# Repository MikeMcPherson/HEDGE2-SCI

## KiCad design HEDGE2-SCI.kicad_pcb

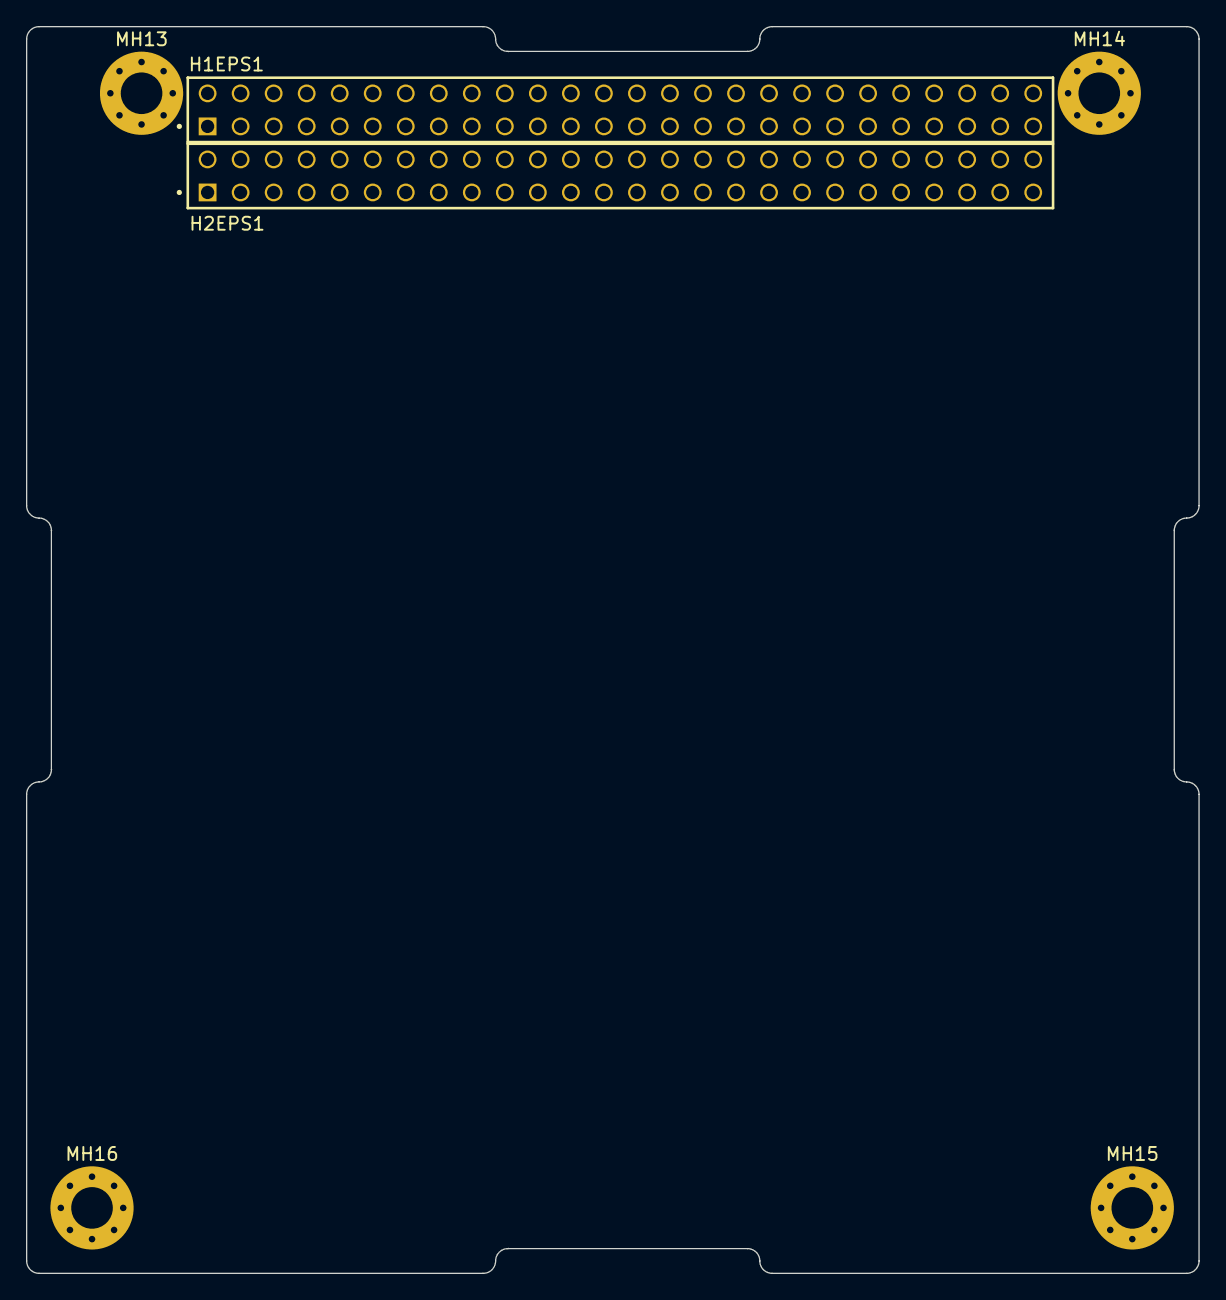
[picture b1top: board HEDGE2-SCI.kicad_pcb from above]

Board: 4 copper layers, 90.2 x 95.9 mm, 6 parts (0 on the bottom side), 4 nets, no tracks yet.

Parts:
H1EPS1, H2EPS1: Conn_02x26_Odd_Even; SAMTEC_ESQ-126-39-G-D
MH13, MH14, MH15, MH16: MountingHole_Pad; MountingHole_3.2mm_M3_Pad_Via

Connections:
/EPS/5V_PERM: H1EPS1.25, H1EPS1.26, H2EPS1.25, H2EPS1.26
/EPS/BATT: H2EPS1.45, H2EPS1.46
/EPS/CHARGE: H2EPS1.43, H2EPS1.44
GND: H1EPS1.29, H1EPS1.30, H1EPS1.31, H1EPS1.32, H2EPS1.29, H2EPS1.30, H2EPS1.31, H2EPS1.32, MH13.1, MH14.1, MH15.1, MH16.1

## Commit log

2025-09-07 Add files
2025-09-07 Change README from HEDGE2-Avionics to HEDGE2-SCI
2025-10-01 Initial Architecture Files
2025-10-03 Add ECAD library
2025-10-15 Initial MAX31856 class (untested) and SensorManager
2025-10-22 ADS1118 and SensorManager Classes
2025-10-28 Add housekeeping sensor interface module
2025-11-11 main.py (3 tasks seperated onto 2 cores)
2025-11-11 Circular Buffer Implementation
2025-11-11 Separation of classes and restructure of architecture
2025-11-11 CLI to lib\comms. comm_manager to core\comms.py
2025-11-16 Buffer title
2025-11-16 Config title
2025-11-16 USB detection loop on core 1 for CLI
2025-11-16 CRC16() and usb detection (untested)
2025-11-16 CLI (calibration TODO and untested)
2025-11-16 add CommManager declaration
2025-11-16 add CLI declaration
2025-11-16 rename
2025-11-18 Implement RS485 communication class
    First version, seems to work
2025-11-18 Add SpaceCAN class
    Still needs to be tewsted, as current board has problems.
2025-11-18 Can't have two threads on one core. Combined comms and CLI task. Fixed sensor acquisition task.
2025-11-18 Dynamic delay to ensure 2 Hz. Apply crc16() to sample
2025-11-19 CLI fixes
2025-11-19 buffer fixes
2025-11-19 Remove test from rs485.py
2025-11-25 Power and status LED
2025-11-25 RS485 & SpaceCAN init
2025-12-02 Setup basic unit test cases
2025-12-02 Status LED error codes
2025-12-02 Move utils.py
2025-12-02 temperature and pressure offsets
2025-12-02 read and apply offsets
2025-12-02 remove config.py
2025-12-02 Calibration support
2025-12-02 Streaming mode
2025-12-02 Self test (limits may need adjusting)
2025-12-02 Increase reboot time
2025-12-04 Remove CommManager
2025-12-04 Remove Config import
2025-12-04 Reformat
2025-12-04 Remove HK offsets
2025-12-04 Remove Calibration Import
2025-12-04 Updated INA238 Conversion Values
2025-12-09 Changed how to check for ina devices for speed
2025-12-10 Buffer hk_temps 4 values not 6, update struct
2025-12-11 Add pressure slopes
2025-12-11 Convert pressure input to kPa, add stream command
2025-12-11 Fix struct pack missing comma
2025-12-12 Safer exiting, struct refactor
2025-12-12 Better USB detection, CRC16 fix
2025-12-12 Struct refactor, stream lock check, calibration fix
2025-12-12 calibration fix
2025-12-12 add all addresses
2025-12-12 Conversion factor fix (for M3021)
2025-12-12 INA fixes
2025-12-12 updated sensors and ads1118 to be differential.
2025-12-13 Pad buffer if less than expected input
2025-12-13 Added dummy read to ads1118 to remove index errors
